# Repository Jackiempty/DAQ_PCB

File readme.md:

# DAQ Datalogging 開發日記

[**Github link**](https://github.com/Jackiempty/Loadcell_PCB)
###### tags:`Avionics`

## 線路連接

## 程式碼
### 校正程式
[Github 連結](https://github.com/Jackiempty/DAQ_PCB/blob/main/code/correction/correction.ino)

### 紀錄程式
[Github 連結](https://github.com/Jackiempty/DAQ_PCB/blob/main/code/DAQ/DAQ.ino)
:::warning
Reviewed by 仲其宇
1. 校正程式最好是可以跟紀錄程式放在一起，通過輸入命令來選擇是否要校正
2. 採樣率太低了。你的 dt 長達 0.1 秒，並且還要每隔 5 次才紀錄。發動機稍一次不過 1~2 秒，這樣採樣點才 4 個，基本無法分析。採樣率至少要到 80Hz。
3. 
其實沒必要進入睡眠模式，我們沒有缺電，徒增資源浪費而已。
4. 
不需要把時間單位轉成秒，從頭到尾用毫秒就好，因為我們需要高響應的結果。
5. 不應該刪掉負數，雖然水平推測出現負數的機率很低。但這也代表如果出現負數，我們可以用來 debug。並且如果有諸如垂直推測的情況(雖然也是幾乎不太可能做)，負數就很重要了。
6. 因為是每紀錄一筆數據就存進 SD，所以有可能出現刷新速度不夠快的情況。因此要做取樣時間的確認，確保取樣率可以保持在 80Hz。<br>如果來不及的話就必須考慮不要每次都開檔、關檔，直到測完才關閉檔案。<br>但同時也會有意點風險，就是當發動機測到一半炸掉，檔案可能會沒存到。但這時用傳輸線回傳的資料就發揮冗於作用了。
7. 建議檔案名稱可以用 define 寫在最前面，方便測試者修改。
8. 程式太多沒用的註解碼了，不方便閱讀。如果有空的話，順便把註解寫寫。
9. 可以加入主動偵測發動機啟動紀錄及熄火停止的功能，方便數據分析。(為防止誤判損失資料，可以保留測試前後 1~10 秒的數據)
:::

### 修改內容  
:::info
reply by 簡誌加  

目前已修改 1~5 以及 7~8 的問題  
至於 6 的話會先進行每次都開關檔能否跑到 80Hz 的測試再決定去留  
:::

## 校正步驟

1. 準備好你的法碼（可以是標準法碼也可以是你是先量好重量的東西，eg:手機、水壺）
2. 將 Loadcell 本體接上接口，按照下圖（使用方法那邊） 
4. 打開校正程式，在程式的起始處填上你的法碼重量並上傳
5. 開啟 Serial Monitor
6. 會有數值一直跳出來
7. 取連續十位取平均

**補充**

7. 打開測量程式，並在程式起始處填上你的校正參數
8. 上傳後再放上法碼檢驗你的參數
9. 如果得到的結果稍有落差的話，你可以
* 在正負五之間做調整，並多驗證幾次
* 如果落差都還是很大的話，建議從步驟2在重來一次

如果驗證的結果沒問題的話

**恭喜你得到了你的校正參數了🎉**

## 使用方法
1. 將電腦接上 Arduino Nano 板
2. 將 Loadcell 本體接上接口，按照下圖

4. 先個別將記憶卡拿下來清除內容再裝回去
5. 打開測量程式，將你的校正參數打在程式起始處
6. 上傳
7. 打開 Serial Monitor 和 Serial Plotter

* Serial Monitor  
  
在 Serial Monitor 我們所看到的數字分別是  
左：時間  
右：重量讀值  
* Serial Plotter  
  
在 Serial Plotter 中，因為它畫圖的方法是把所有值都給予編號，並以編號為橫軸，讀值為縱軸列出  
所以這個圖的判讀法就是固定橫軸的值之後得到的兩個縱軸數值就是時間和重量，而非橫軸為時間，縱軸為重量  
## 洞洞板焊接結果

這算是我焊的第一塊洞洞板，中間歷經了使用 AWG30 的線、焊錯要解焊、換使用有橡膠套的線，最後花了總時長大概四小時左右將它焊完。

經過測試，是可以運作的，沒有短路的情況發生，算是一個好的開始  
下一步應該就是要開始設計集成電路板了，也是一個我沒做過的事

## 外殼
用 Solidworks 簡單畫了一個外殼，除了有仔細算過整個總成的 Dimension 並畫出可以 fit 整片洞洞板上去，還在殼上弄出一些洞可以穿線路，最後還設計了一個可以卡上去的蓋子  

在計算總成的 Dimension 時也順便把它畫出來以方便比對外殼的大小有沒有畫對  

# PCB 開發紀錄
作完了自己把所有元件焊在一片板子上之後，更進一步整合就是要作 PCB 了

## Schematic
### ver1.0

### ver1.5

### Update
:::info
:information_source: Update  
更 1.1 版：  
由於原本的 usb-serial 轉換器 FT232RL 聽說不好買  
在組長的建議下我換成 CH340C，之後便修改了 RX/TX 的 LED 線路位置  
以及原本 SD_Card Module 所使用的 3.3V 換成了 5V

更 1.2 版：  
我將原本存在於 Arduino nano 功能中的 VCC 轉 5V 功能給拿掉了，原本 VCC 是外接電源轉給內部 5V 使用，拿掉之後讓供電的工作交給，USB_C 就好了，省掉一些不必要的線路  
另外，原本以為是熱敏電阻的 RV1 其實是 Fuse，所以進行修正，現在是用 Schotty Diode 替代，變成 D3  

更 1.3 版：  
RESET 電路的上拉電阻畫錯了，進行修正，連同 PCB 一起  
另外還加上了 M3 鎖點  

更 1.4 版：  
將多餘的線路刪掉（VBUS、SS1P3L），並優化電容配置  

更 1.5 版：  
將 HX711 上的 rate 腳位做成上拉電阻，以增加可以改變運作頻率的選擇  

更 1.6 版：  
增加一個額外的 UART 通道，可以外接一個 GPS 算降落傘的 CD (Coefficient Drag)
:::

## Footprint

Footprint 的選擇其實有遇到一些困難  
比較有問題的幾個分別是
* SS1P3L
* 74125
* HX711
* CH340C

等，幾個比較特定功能的  
由於我這是第一次做這個工作，所以對於 Package 的辨識以及選擇較缺乏經驗  
所以花了一點時間研究和問問題  

總之目前的配置大概是這樣，**作為讀者的你如果有發現任何問題請不吝賜教**

## PCB Layout (ver1.3)
**Refer to sch ver1.5**  
:::info
:information_source: Update  
ver1.1 導了圓角  
ver1.2 將有銳角的線路修鈍，並做些小優化  
ver1.3 參照 sch ver1.5  
ver1.4 參照 sch ver1.6 並將圓角推至角落改善美觀  
:::

## 待更新：
- [x] HX711： Rate 腳位要做 either 上拉 or 下拉  
- [x] 增加 UART 接口  
- [x] 修改程式碼，改進 data logging 的品質  

# PT
由於後來需要加上艙壓的測量，所以引進了 PT `(pressure transducer)` 的讀取功能進到板子裡，這裡先上 PT 的規格：  
* [**Datasheet**](https://www.yuden.com.tw/uploadfiles/423/Products/Catalog/eyc-huba-511_pressure_sensor-20190409.pdf)
* 種類：電流式
* 電流範圍：4 ~ 20 mA
* 壓力範圍：~ 100 bar
* 供電：8 ~ 33 VDC

## 使用方式
我們採取的作法是使用 Arduino 板子上的 ADC 作為我們讀取電壓的接口，由於 Arduino 的 ADC 能夠讀取的電壓範圍是 0 ~ 5 V，所以配合電流的範圍 4 ~ 20 mA 我們得到
$5V \div 0.02A = 250 \Omega$，於是我們便在 ADC 的讀取接口與地線之間串了 250 $\Omega$ 的電阻並讓 ADC 的讀值會介於 1 ~ 5 V 之間，並透過線性的對應關係就可以知道壓力的值為多少。  

然而，由於我們的供電沒辦法完全給夠 5V，所以最後的最高位參考電壓會變成是供電的電壓，也就是 4.5V，並且不穩定。為了讓參考電壓是穩定的，我們將 `analogRead()` 的參考電壓設為 1.1V，方法是透過在 `setup()` 裡面加上一段：
```cpp
void setup() {
    .......
    analogReference(INTERNAL);
    .......
}
```
詳細說明請見[這裡](https://www.arduino.cc/reference/en/language/functions/analog-io/analogreference/)

## 程式碼
不囉唆，直接上：
```cpp
float read_pt() {
  float raw = analogRead(A1);
  float Max = MAX;
  float Min = 1;
  float V1R1_actual = 1.1;
  float Max_ADC = 0.02 * 47 / V1R1_actual * 1023;
  float Bar_1_Value = 224;
  float slope = float(Max - Min) / float(Max_ADC - Bar_1_Value);
  float pressure = (Min + slope * (raw - Bar_1_Value)) * 1000.0;
  return pressure;
}
```

原理很簡單，讀取到的電壓為 1 ~ 1.1 V，對應到板子所顯示的數字是約 204 ~ 1023，所以程式碼裡面 `raw` 的範圍就會是 204 ~ 1023。但由於我們的電阻沒辦法剛剛好就是精準的 55 Ohms，所以我們的斜率實際上是要用 $\Delta$壓力 / $\Delta$角位讀值，才能夠精準地讓讀值跟我們所求的數值互相對應。  

剩下的就是線性對應的算式，沒什麼好解釋的，反正重點就是最後 `pressure` 這個變數就會是我們要求的氣壓值。  

## 測試結果
前幾天 7/4 的時候我有去柏漢的實驗室用那邊的鋼瓶給氣壓去測 PT 是否能正常運作，那時候我們上面接的電阻實際量出來約為 242，所以對應到前面程式碼的話 204 就會變成 197，除此之外都一樣，量出來的數值雖然會浮動，但整體的範圍還算正確。

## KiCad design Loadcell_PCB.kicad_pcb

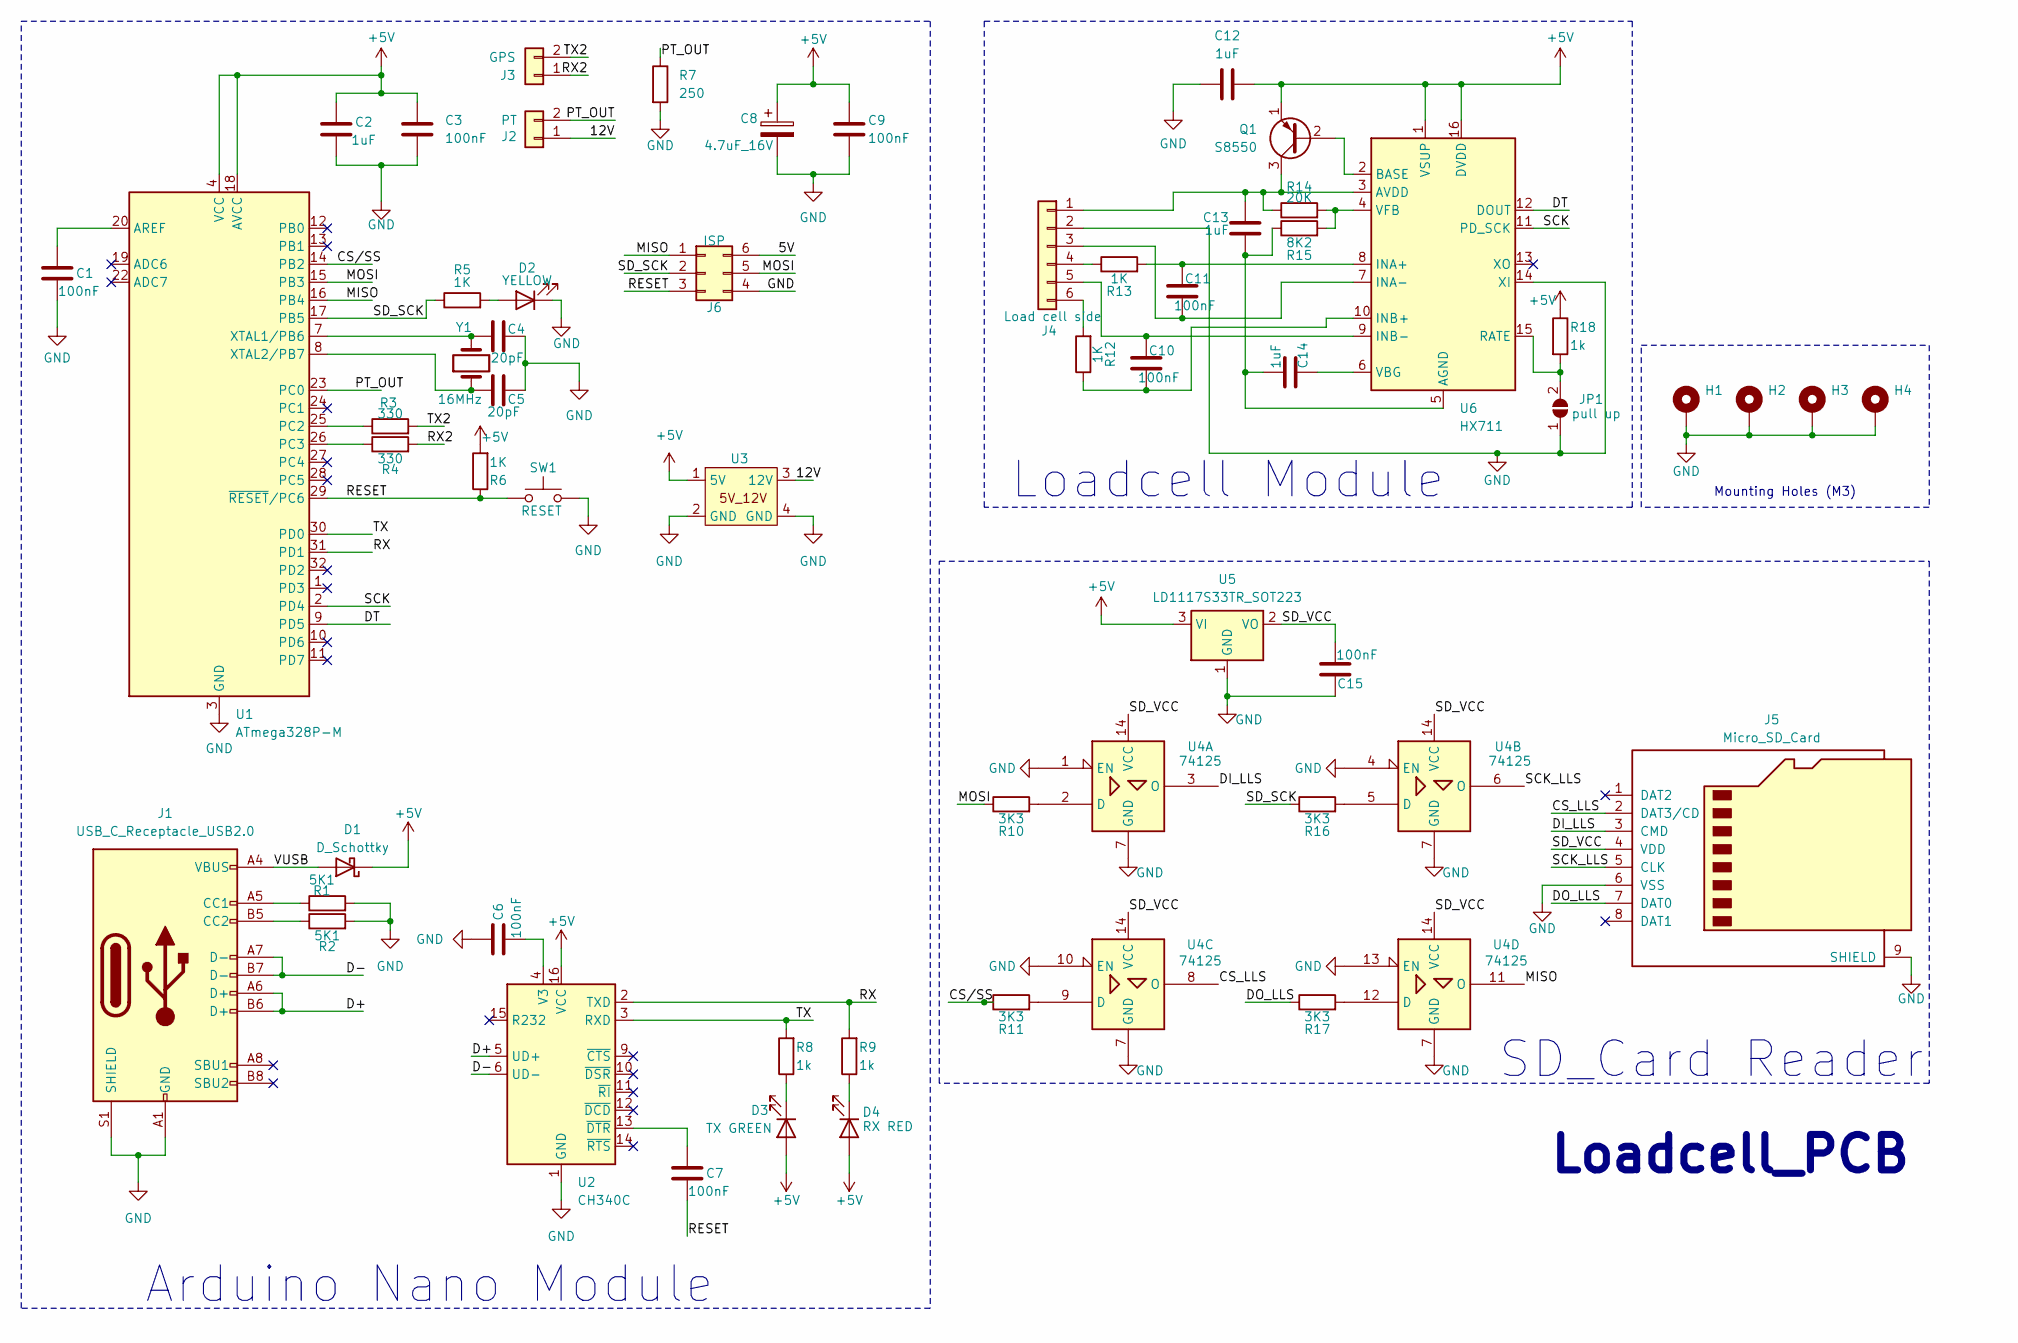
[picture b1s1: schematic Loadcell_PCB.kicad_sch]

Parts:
C1, C3, C6, C7, C9, C10, C11, C15: 100nF; C_0805_2012Metric_Pad1.18x1.45mm_HandSolder
C2, C12, C13, C14: 1uF; C_0805_2012Metric_Pad1.18x1.45mm_HandSolder
C4, C5: 20pF; C_0805_2012Metric_Pad1.18x1.45mm_HandSolder
C8: 4.7uF_16V; CP_Elec_4x3
D1: D_Schottky; LED_0805_2012Metric_Pad1.15x1.40mm_HandSolder
D2: YELLOW; LED_0805_2012Metric_Pad1.15x1.40mm_HandSolder
D3: TX GREEN; LED_0805_2012Metric_Pad1.15x1.40mm_HandSolder
D4: RX RED; LED_0805_2012Metric_Pad1.15x1.40mm_HandSolder
H1, H2, H3, H4: MountingHole_Pad; MountingHole_3.2mm_M3_Pad
J1: USB_C_Receptacle_USB2.0; USB_C_Receptacle_GCT_USB4105-xx-A_16P_TopMnt_Horizontal
J2: PT; PinHeader_1x02_P2.54mm_Horizontal
J3: GPS; PinHeader_1x02_P2.54mm_Horizontal
J4: Load cell side; PinHeader_1x06_P2.54mm_Horizontal
J5: Micro_SD_Card; microSD_HC_Molex_104031-0811
J6: ISP; PinHeader_2x03_P1.27mm_Vertical
JP1: pull up; SolderJumper-2_P1.3mm_Open_RoundedPad1.0x1.5mm
Q1: S8550; TO-92_Inline
R1, R2: 5K1; R_0805_2012Metric_Pad1.20x1.40mm_HandSolder
R3, R4: 330; R_0805_2012Metric_Pad1.20x1.40mm_HandSolder
R5, R6, R12, R13: 1K; R_0805_2012Metric_Pad1.20x1.40mm_HandSolder
R7: 250; R_0805_2012Metric_Pad1.20x1.40mm_HandSolder
R8, R9, R18: 1k; R_0805_2012Metric_Pad1.20x1.40mm_HandSolder
R10, R11, R16, R17: 3K3; R_0805_2012Metric_Pad1.20x1.40mm_HandSolder
R14: 20K; R_0805_2012Metric_Pad1.20x1.40mm_HandSolder
R15: 8K2; R_0805_2012Metric_Pad1.20x1.40mm_HandSolder
SW1: RESET; SW_SPST_CK_RS282G05A3
U1: ATmega328P-M; TQFP-48-1EP_7x7mm_P0.5mm_EP5x5mm_ThermalVias
U2: CH340C; SOIC-16_3.9x9.9mm_P1.27mm
U3: DC2DC
U4: 74125; SOIC-14_3.9x8.7mm_P1.27mm
U5: LD1117S33TR_SOT223; SOT-223-3_TabPin2
U6: HX711; SOP-16_3.9x9.9mm_P1.27mm
Y1: 16MHz; Crystal_SMD_HC49-SD

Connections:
+5V: C2.2, C3.2, C8.1, C9.1, C12.2, D1.1 (K), D3.2 (A), D4.2 (A), Q1.1 (E), R6.2, R18.1, U1.4 (VCC), U1.6 (VCC), U1.18 (AVCC), U2.16 (VCC), U3.1 (5V), U5.3 (VI), U6.1 (VSUP), U6.16 (DVDD)
/5V: J6.6
/12V: J2.1, U3.3 (12V)
/CS_LLS: J5.2 (DAT3/CD), U4.8 (O)
/CS/SS: R11.1, U1.14 (PB2)
/D+: J1.A6 (D+), J1.B6 (D+), U2.5 (UD+)
/D-: J1.A7 (D-), J1.B7 (D-), U2.6 (UD-)
/DI_LLS: J5.3 (CMD), U4.3 (O)
/DO_LLS: J5.7 (DAT0), R17.1
/DT: U1.9 (PD5), U6.12 (DOUT)
/MISO: J6.1, U1.16 (PB4), U4.11 (O)
/MOSI: J6.5, R10.1, U1.15 (PB3)
/PT_OUT: J2.2, R7.1, U1.23 (PC0)
/RESET: C7.2, J6.3, R6.1, SW1.1, U1.29 (~RESET/PC6)
/RX: R9.2, U1.31 (PD1), U2.2 (TXD)
/RX2: J3.1, R4.2
/SCK: U1.2 (PD4), U6.11 (PD_SCK)
/SCK_LLS: J5.5 (CLK), U4.6 (O)
/SD_SCK: J6.2, R5.1, R16.1, U1.17 (PB5)
/SD_VCC: C15.1, J5.4 (VDD), U4.14 (VCC), U5.2 (VO)
/TX: R8.2, U1.30 (PD0), U2.3 (RXD)
/TX2: J3.2, R3.2
/VUSB: D1.2 (A), J1.A4 (VBUS), J1.A9 (VBUS), J1.B4 (VBUS), J1.B9 (VBUS)
GND: C1.2, C2.1, C3.1, C4.2, C5.2, C6.1, C8.2, C9.2, C12.1, C15.2, D2.1 (K), H1.1, H2.1, H3.1, H4.1, J1.A1 (GND), J1.A12 (GND), J1.B1 (GND), J1.B12 (GND), J1.S1 (SHIELD), J4.2, J5.6 (VSS), J5.9 (SHIELD), J6.4, JP1.1 (A), R1.2, R2.2, R7.2, SW1.2, U1.3 (GND), U1.5 (GND), U1.21 (GND), U1.33 (GND), U2.1 (GND), U3.2 (GND), U3.4 (GND), U4.1 (EN), U4.4 (EN), U4.7 (GND), U4.10 (EN), U4.13 (EN), U5.1 (GND), U6.14 (XI)
unnamed: D2.2 (A), R5.2
unnamed: D3.1 (K), R8.1
unnamed: D4.1 (K), R9.1
unnamed: J1.A5 (CC1), R1.1
unnamed: J1.B5 (CC2), R2.1
unnamed: C13.2, J4.1, Q1.3 (C), R14.1, U6.3 (AVDD)
unnamed: C11.1, J4.3, U6.7 (INA-)
unnamed: J4.4, R13.1
unnamed: C10.2, J4.5, U6.9 (INB-)
unnamed: J4.6, R12.2
unnamed: JP1.2 (B), R18.2, U6.15 (RATE)
unnamed: Q1.2 (B), U6.2 (BASE)
unnamed: C1.1, U1.20 (AREF)
unnamed: R3.1, U1.25 (PC2)
unnamed: R4.1, U1.26 (PC3)
unnamed: C4.1, U1.7 (XTAL1/PB6), Y1.2
unnamed: C5.1, U1.8 (XTAL2/PB7), Y1.1
unnamed: C6.2, U2.4 (V3)
unnamed: C7.1, U2.13 (~DTR)
unnamed: R10.2, U4.2 (D)
unnamed: R16.2, U4.5 (D)
unnamed: R11.2, U4.9 (D)
unnamed: R17.2, U4.12 (D)
unnamed: C13.1, C14.1, R15.1, U6.5 (AGND)
unnamed: C11.2, R13.2, U6.8 (INA+)
unnamed: C10.1, R12.1, U6.10 (INB+)
unnamed: C14.2, U6.6 (VBG)
unnamed: R14.2, R15.2, U6.4 (VFB)

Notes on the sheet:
SD_Card Reader
Loadcell Module
Mounting Holes (M3)
Arduino Nano Module
Loadcell_PCB

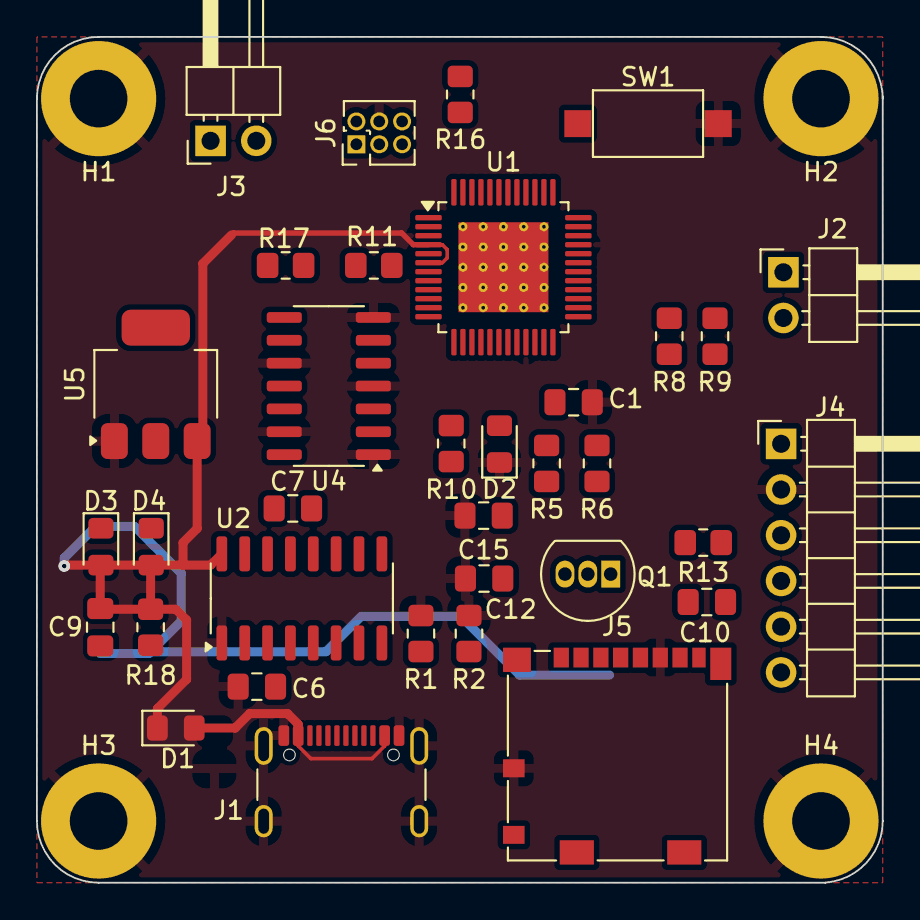
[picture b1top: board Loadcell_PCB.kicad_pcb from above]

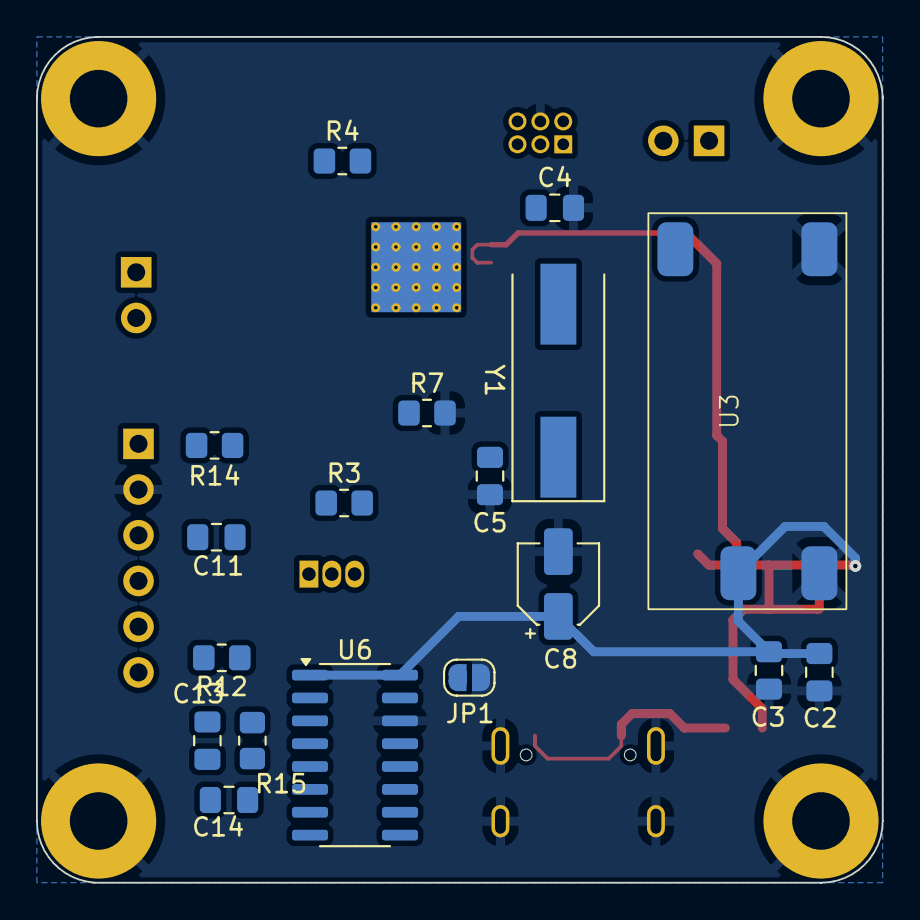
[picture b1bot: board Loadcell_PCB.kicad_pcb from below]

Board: 2 copper layers, 47.0 x 47.0 mm, 57 parts (18 on the bottom side), 51 nets.

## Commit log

2024-02-12 loadcell_PCB git repo first commit
2024-02-12 some cleanup and add .gitignore
2024-02-12 further cleanup for temp file
2024-02-12 further cleanup (.kicad_prl)
2024-02-12 last changed at Feb 13, 2024 2:24 AM, pushed by Jackiempty
    Add readme which is connected to hackmd
2024-02-13 last changed at Feb 14, 2024 1:24 AM, pushed by Jackiempty
    minor update on readme
2024-02-14 last changed at Feb 14, 2024 11:38 PM, pushed by Jackiempty
    add github link
2024-02-14 fix html image issue
2024-02-14 Found that html size controlling does not work, so give up tying
2024-02-14 fix the image problem
    compressed the image from over 10 mb to about 6mb
2024-02-14 4th attempt
    well, it just doesn't work, so i keep tying.
    hope it will work this time
2024-02-14 5th attempt
2024-02-14 7th attempt
    use a cheeting way: screen shot
2024-02-17 add case CAD information
2024-02-19 Add loadcell weight loading plot
2024-02-20 add case 3D cad
2024-02-20 add 3D CAD in stl
2024-02-20 modify CAD back to no legs
2024-02-22 Add to-do list at the end of the page
2024-03-05 Add pull-up resistor at rate pin on HX711 IC
    Since HX711 can work in a higher frequency with rate pin pulled up, so I
    add a optional structure that can select between two frequency by
    soldering a ball at solder-jump bridge
2024-03-06 Minor update on content
    Fix the dated content of the descruption of the PCB version
2024-04-18 Add an extra UART channel for GPS
    In order to recieve GPS and serail print signals at the same time,
    we need more than only one UART channel which is used as the serial
    print channel by default, So now the second UART channel is added
    and the implementation will be done by software.
2024-04-18 last changed at Apr 18, 2024 7:28 PM, pushed by Jackiempty
2024-04-18 Adjust schmetic layout
2024-04-18 Update unsaved record to the current commit
2024-04-18 Add new objective
    Since the current code of data logging is totally a piece of shit, so maybe someday when I have time I will improve it.
2024-04-27 Add comment and modified content
2024-04-27 Add STEP of PCB and arduino code
    A step file of the pcb is export for any free to use, and also the
    arduino code is included for the intergration of the board and the
    program.
2024-04-29 Change spoiler grammer to HTML for github compatibility
2024-05-03 Update windows files and stuff
2024-05-17 Add size marking on pcb
2024-06-25 Include correction code and reorder the file structure
2024-06-25 Fix minor bugs on loadcell.ino
2024-06-29 Prepare for next revision - PT initial edit
2024-07-01 Add new symbol and footprint for DC2DC converter
    In order to power PT which requires 8V ~ 12V power supply, an 5V_12V
    DC2DC converter in added into the schematic. Since the converter is
    custom manufactured by an independent company, the correspond data
    is not included in the Kicad library. So I have to draw it by my self.
    Now, both symbol and footprint are finished, the next step is to
    redraw the whole PCB layout and make it even more compact.
2024-07-02 Add new SD card slot 3D cad and start re-laying the PCB
    New SD card slot has also no 3D cad in standard library, so I added
    one. Also, new layout has started, and this commit is a save record
    in case the app crashes which happens quite frequently at version 8.
2024-07-03 Add PT reading function into loadcell program, waiting for test
2024-07-04 Finish PT reader and printer, comment all SD_card function temparary
2024-07-05 Remove SD logging function temparary and use minicom to log serial monitor instead
2024-07-08 Remove redundant pretty files
2024-07-12 Re-layout progress at 15% and add connector pin for in system programming
2024-07-16 Stage 1 layout and modify offset minimum raw number for PT
2024-07-18 Optimize read_PT() for more realistic condition
2024-07-22 Set analog read pin reference voltage to 1.1V
    Since the upper limit voltage of arduino uno is 4.5V, the reference
    voltage cannot be 5.5V anymore else it becomes imprecise, so the
    reference voltage of the analog read pin is set to 1.1V, which means
    that the resistance on the board also has to be replaced with new
    value.
    In addition, .vscode configuration file is ignored by adding it to
2024-07-24 Change PT formula for 1.1V analogRead
2024-07-24 Update analogRead explanation to be compatible with 1.1V reference
2024-08-05 Change Bar_1_value to theoretically correct value
2024-10-07 Upload correction code, should be used individually
2024-10-07 Update PCB conventionally
2024-10-07 Change file name: Loadcell -> DAQ
2024-11-11 Remove calibration functions in this program, keep it seperated
2024-11-11 last changed at Nov 11, 2024 9:00 AM, pushed by Jackiempty
2024-12-12 Test embedded pdf function
2024-12-12 Confirm that embedded pdf is not available in github readme.md page
